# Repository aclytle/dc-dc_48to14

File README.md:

w7yh_48_buck
============

48 volt to 19v/14v buck converter

Made with EAGLE 7.2

Mouser BOM: https://www.mouser.com/ProjectManager/ProjectDetail.aspx?AccessID=fb4fd6b050

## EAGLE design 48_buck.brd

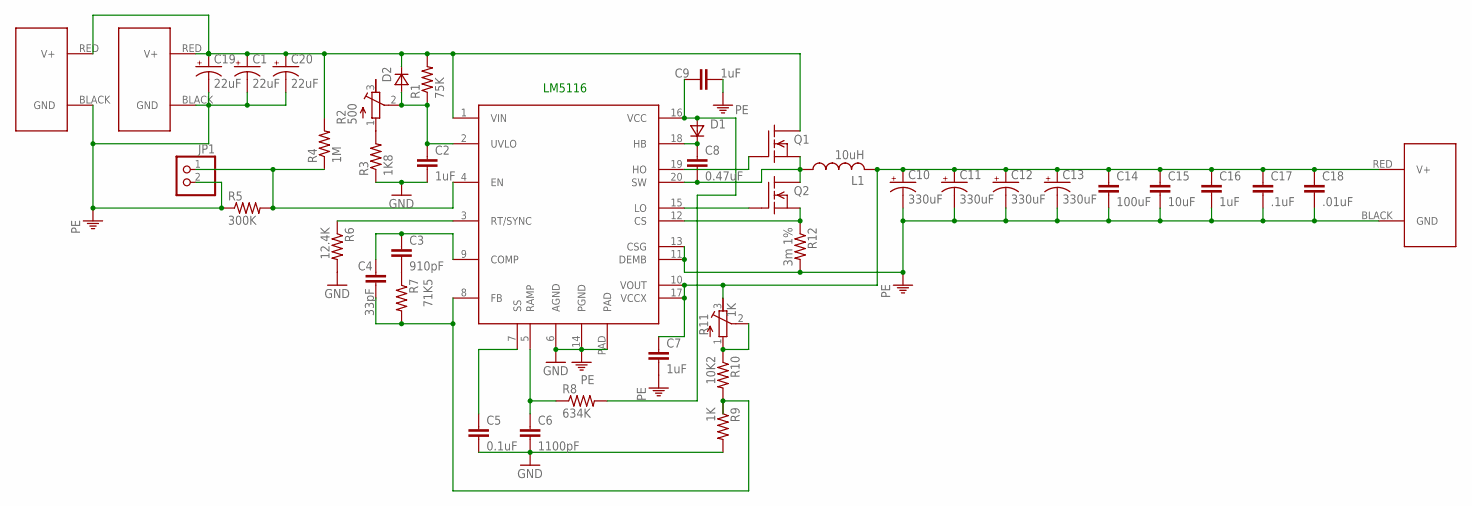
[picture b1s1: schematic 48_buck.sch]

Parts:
C1, C19, C20: 22uF; E3,5-8
C2, C9, C16: 1uF; C1206
C3: 910pF; C0805
C4: 33pF; C0805
C5: 0.1uF; C0805
C6: 1100pF; C0805
C7: 1uF; C0805
C8: 0.47uF; C0805
C10, C11, C12, C13: 330uF; E5-10,5
C14: 100uF; C1210
C15: 10uF; C1206
C17: .1uF; C0805
C18: .01uF; C0805
D1, D2: VAR2SOT23; SOT-23
J1, J2: POWERPOLE_POWER45A_HORIZONTAL_DRILL; POWERPOLE_PAIR_45A_HORIZ_HOLE
J3: POWERPOLE_POWER10AWG; POWERPOLE_PAIR_10AWG
JP1: PINHD-1X2; 1X02
L1: 10uH; AIRD-03
LM5116: LM5116; TSSOP20
Q1, Q2: BUZ21; TO220
R1: 75K; R1206
R2: 500; 3303X-3
R3: 1K8; R1206
R4: 1M; R0805
R5: 300K; R0805
R6: 12.4K; R0805
R7: 71K5; R0805
R8: 634K; R0805
R9: 1K; R0805
R10: 10K2; R2818
R11: 1K; 3303X-3
R12: 3m 1%; R0805

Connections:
GND: C2.2, C5.2, C6.2, LM5116.6 (AGND), LM5116.14 (PGND), LM5116.PAD, R3.1, R6.2, R9.2
unnamed: R2.1 (A), R3.2
unnamed: JP1.1, LM5116.4 (EN), R4.1, R5.2
unnamed: C5.1, LM5116.7 (SS)
unnamed: C9.1, D1.3 (A), LM5116.16 (VCC), R8.2
unnamed: C3.2, R7.1
unnamed: LM5116.3 (RT/SYNC), R6.1
unnamed: C3.1, C4.1, LM5116.9 (COMP)
unnamed: LM5116.15 (LO), Q2.1 (G)
unnamed: C6.1, LM5116.5 (RAMP), R8.1
unnamed: C8.1, D1.1 (C), LM5116.18 (HB)
unnamed: C2.1, D2.3 (A), LM5116.2 (UVLO), R1.1, R2.2 (S)
unnamed: LM5116.19 (HO), Q1.1 (G)
unnamed: C7.1, C10.+, C11.+, C12.+, C13.+, C14.1, C15.1, C16.1, C17.1, C18.1, J1.RED (V+), L1.P$2 (2), LM5116.10 (VOUT), LM5116.17 (VCCX), R11.3 (E)
unnamed: LM5116.12 (CS), Q2.3 (S), R12.1
unnamed: R10.P$1 (1), R11.1 (A), R11.2 (S)
unnamed: C1.+, C19.+, C20.+, D2.1 (C), J2.RED (V+), J3.RED (V+), LM5116.1 (VIN), Q1.2 (D), R1.2, R4.2
unnamed: C4.2, LM5116.8 (FB), R7.2, R9.1, R10.P$2 (2)
unnamed: C8.2, L1.P$1 (1), LM5116.20 (SW), Q1.3 (S), Q2.2 (D)
PE: C1.-, C7.2, C9.2, C10.-, C11.-, C12.-, C13.-, C14.2, C15.2, C16.2, C17.2, C18.2, C19.-, C20.-, J1.BLACK (GND), J2.BLACK (GND), J3.BLACK (GND), JP1.2, LM5116.11 (DEMB), LM5116.13 (CSG), R5.1, R12.2

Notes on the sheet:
LM5116

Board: 2 copper layers, 42 parts (0 on the bottom side), 20 nets, no tracks yet.

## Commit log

2015-03-25 Created initial files
2015-03-25 Mostly done with first iteration
2015-03-26 Update readme to identify eagle version used
2015-06-14 Update with values from quickstart sheet
2015-06-14 Add sheets for calculating values
2015-06-14 Add BOM link from Mouser
2015-06-23 Verified schematic, added components to library, started layout
